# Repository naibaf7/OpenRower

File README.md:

# OpenRower

An open-source rowing monitor for any rowing machine. A sensor on the flywheel sends the timing of each
pulse to an Android app. The app works out pace, power, stroke rate and distance, draws a live force curve
and records your workouts.

## Features

- **Workout modes:** free rowing, set distance, set time, target pace, and custom interval workouts built
  from segments.
- **Live display:**
  - pace per 500 m (current and average), stroke rate, power in watts or calories;
  - time and distance, elapsed and remaining, and the projected finish;
  - heart rate.
- **Charts:** a force curve for every stroke, and a stroke-by-stroke bar chart of power with heart-rate zones.
- **Custom workouts:** a timeline editor with a target pace per segment, music per segment (matched to your
  stroke rate by BPM, from a folder or M3U playlist) and a spoken countdown.
- **Training history** with splits for every workout.
- **Heart rate** from BLE chest straps that use the standard Heart Rate service (developed with a Polar H7).
- **Physics:** the drag factor is measured on every stroke. Flywheel inertia and the distance factor are
  stored per machine profile. You can calibrate the distance factor against the machine's own monitor.
- **Built-in profiles** for the Concept2 Model C, D and E and the Infinity R70.
- **Test mode** with simulated data, so you can try the app without any hardware.

## Hardware

You need one of these to connect a rowing machine:

| | OpenRower sensor board | DIY Arduino build |
|---|---|---|
| Board | ESP32-C3 board in [`hardware/`](hardware/openrower_sensor_circuit.md) | Arduino Nano + BT05/HM-10 BLE module |
| Sensor | Plug the machine's sensor into its 2.5 mm jack: hall sensors at 3.3 V or 5 V, Concept2 Model C pickup coil, Concept2 Model D/E generator | Hall sensor on pin 2, magnets on the flywheel (3 magnets 120° apart) |
| Link to the phone | BLE, or USB-C via USB-OTG | BLE, or USB via USB-OTG |
| Firmware | [`OpenRowerESP32/`](OpenRowerESP32/README.md) | [`OpenRowerArduino/`](OpenRowerArduino/OpenRowerArduino.ino) |

The app chooses the sensor board's input mode from the machine profile, or detects what is plugged in.
The board is designed so that no mode choice can damage it, the phone or the rowing machine. The one
exception is giving 5 V to a hall sensor that is only rated for 3.3 V, so the app asks before it switches
to 5 V.

## Getting started

1. **Install the app.** It needs Android 12 or newer. A Google Play release, published by Smartapes, is
   in preparation. Until then, build it from source: connect your phone with USB debugging on, then run
   ```
   ./gradlew installDebug
   ```
   or open the project in Android Studio and press Run.
2. **Set up the hardware.**
   - Sensor board: order it as described in
     [`hardware/openrower_sensor_circuit.md`](hardware/openrower_sensor_circuit.md) §9. Then flash the
     firmware image from the [releases page](https://github.com/naibaf7/OpenRower/releases), or build it
     yourself ([`OpenRowerESP32/README.md`](OpenRowerESP32/README.md)).
   - Arduino: wire up the hall sensor and BT module as described at the top of the sketch, then upload it.
     The sketch sets the BT module to the right baud rate by itself.
3. **In the app:**
   1. In **Settings**, pick or create a machine profile.
   2. Choose the rowing device (Scan BLE) and, for the sensor board, the sensor input.
   3. Go back to **Workout Setup**, pick a mode and start rowing.

To try the app without hardware, turn on **Test Mode** on the Workout Setup screen.

## Status

- **App and Arduino build:** in use on an Infinity R70 fitted with a hall sensor.
- **Sensor board (rev 2) and ESP32 firmware:** designed, and the firmware compiles, but neither has been
  tested on real hardware yet. Start with the bring-up checklist in
  [`hardware/openrower_sensor_circuit.md`](hardware/openrower_sensor_circuit.md) §10.
- **Concept2 profiles:** the constants come from OpenRowingMonitor's rower profiles and have not been checked
  on a real machine yet.

## Repository layout

| Path | Contents |
|---|---|
| `app/` | Android app (Kotlin) |
| `OpenRowerESP32/` | Firmware for the sensor board and the serial/BLE protocol |
| `OpenRowerArduino/` | Firmware for the Arduino Nano + BT05 build |
| `hardware/` | Sensor board: KiCad schematic and routed board, schematic PDF, generator scripts, design notes. Production files (gerbers, BOM, CPL) are on the releases page. |

## Privacy

OpenRower has no internet access. Your workouts stay on your device. See [PRIVACY.md](PRIVACY.md).

## Contributing

Contributions are welcome. See [CONTRIBUTING.md](CONTRIBUTING.md). Maintainers release as described in
[RELEASING.md](RELEASING.md).

## License

- **Software** (the app, both firmwares, `hardware/tools/`): [MIT](LICENSE). Third-party licences: in the
  app under Settings → Open-Source Licenses, and for firmware images in
  [OpenRowerESP32/THIRD_PARTY_NOTICES.txt](OpenRowerESP32/THIRD_PARTY_NOTICES.txt).
- **Hardware** (the sensor board design in `hardware/`): [CERN-OHL-S v2](hardware/LICENSE). If you make
  boards for others, keep the source location visible; see [hardware/NOTICE](hardware/NOTICE).

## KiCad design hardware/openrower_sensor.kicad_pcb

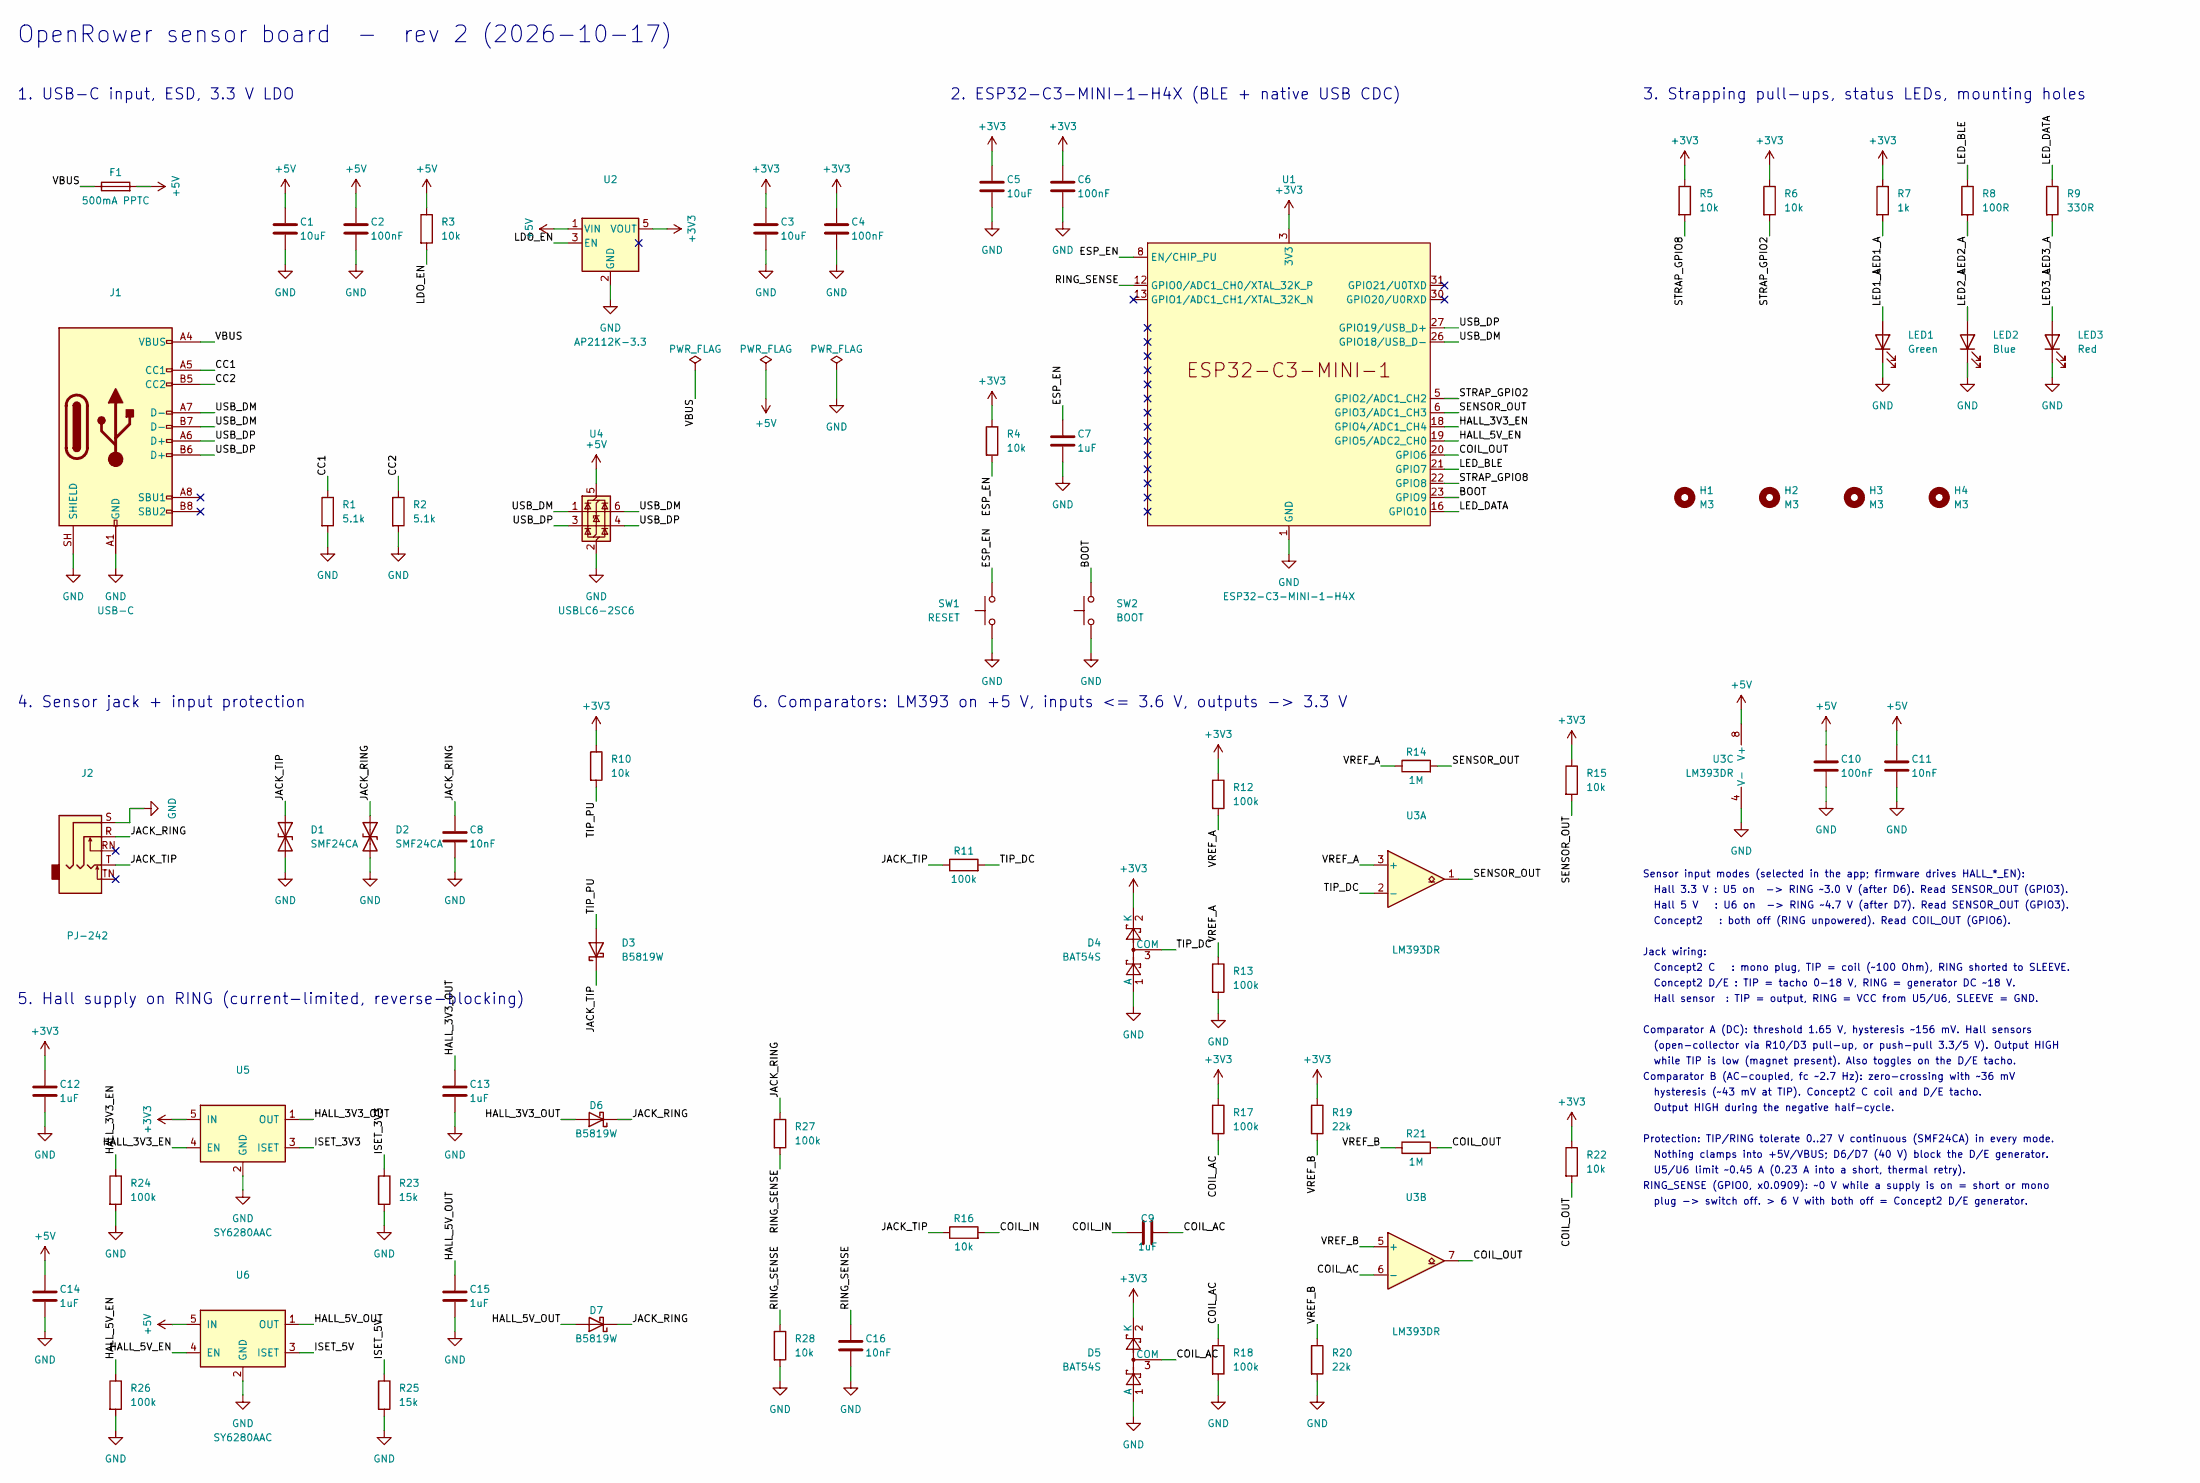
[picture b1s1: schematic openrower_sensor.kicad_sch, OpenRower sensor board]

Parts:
C1, C3, C5: 10uF; C_0603_1608Metric; MPN CL10A106KP8NNNC; LCSC C19702
C2, C4, C6, C10: 100nF; C_0402_1005Metric; MPN CL05B104KO5NNNC; LCSC C1525
C7, C12, C13, C14, C15: 1uF; C_0402_1005Metric; MPN CL05A105KA5NQNC; LCSC C52923
C8, C11, C16: 10nF; C_0402_1005Metric; MPN CL05B103KB5NNNC; LCSC C15195
C9: 1uF; C_0603_1608Metric; MPN CL10A105KB8NNNC; LCSC C15849
D1, D2: SMF24CA; D_SOD-123F; MPN SMF24CA; LCSC C123811
D3, D6, D7: B5819W; D_SOD-123; MPN B5819W SL; LCSC C8598
D4, D5: BAT54S; SOT-23; MPN BAT54S,215; LCSC C47546
F1: 500mA PPTC; Fuse_1206_3216Metric; MPN nSMD050-33V; LCSC C70077
H1, H2, H3, H4: M3; MountingHole_3.2mm_M3
J1: USB-C; USB_C_Receptacle_HRO_TYPE-C-31-M-12_Edge; MPN TYPE-C-31-M-12; LCSC C165948
J2: PJ-242; Jack_2.5mm_SHOUHAN_PJ-242; MPN PJ-242; LCSC C431536
LED1: Green; LED_0603_1608Metric; MPN XL-1608UGC-04; LCSC C965804
LED2: Blue; LED_0603_1608Metric; MPN XL-1608UBC-04; LCSC C965807
LED3: Red; LED_0603_1608Metric; MPN KT-0603R; LCSC C2286
R1, R2: 5.1k; R_0402_1005Metric; MPN 0402WGF5101TCE; LCSC C25905
R3, R4, R5, R6, R10, R15, R22, R28: 10k; R_0402_1005Metric; MPN 0402WGF1002TCE; LCSC C25744
R7: 1k; R_0402_1005Metric; MPN 0402WGF1001TCE; LCSC C11702
R8: 100R; R_0402_1005Metric; MPN 0402WGF1000TCE; LCSC C25076
R9: 330R; R_0402_1005Metric; MPN 0402WGF3300TCE; LCSC C25104
R11, R12, R13, R17, R18, R24, R26, R27: 100k; R_0402_1005Metric; MPN 0402WGF1003TCE; LCSC C25741
R14, R21: 1M; R_0402_1005Metric; MPN 0402WGF1004TCE; LCSC C26083
R16: 10k; R_0603_1608Metric; MPN 0603WAF1002T5E; LCSC C25804
R19, R20: 22k; R_0402_1005Metric; MPN 0402WGF2202TCE; LCSC C25768
R23, R25: 15k; R_0402_1005Metric; MPN 0402WGF1502TCE; LCSC C25756
SW1: RESET; SW_Push_1P1T_XKB_TS-1187A; MPN TS-1187A-B-A-B; LCSC C318884
SW2: BOOT; SW_Push_1P1T_XKB_TS-1187A; MPN TS-1187A-B-A-B; LCSC C318884
U1: ESP32-C3-MINI-1-H4X; ESP32-C3-MINI-1; MPN ESP32-C3-MINI-1-H4X; LCSC C41349510
U2: AP2112K-3.3; SOT-23-5; MPN AP2112K-3.3TRG1; LCSC C51118
U3: LM393DR; SOIC-8_3.9x4.9mm_P1.27mm; MPN LM393DR; LCSC C67470
U4: USBLC6-2SC6; SOT-23-6; MPN USBLC6-2SC6; LCSC C7519
U5, U6: SY6280AAC; SOT-23-5; MPN SY6280AAC; LCSC C55136

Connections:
+3V3: C3.1, C4.1, C5.1, C6.1, C12.1, D4.2 (K), D5.2 (K), R4.1, R5.1, R6.1, R7.1, R10.1, R12.1, R15.1, R17.1, R19.1, R22.1, U1.3 (3V3), U2.5 (VOUT), U5.5 (IN)
+5V: C1.1, C2.1, C10.1, C11.1, C14.1, F1.2, R3.1, U2.1 (VIN), U3.8 (V+), U4.5 (VBUS), U6.5 (IN)
/BOOT: SW2.2, U1.23 (GPIO9)
/CC1: J1.A5 (CC1), R1.1
/CC2: J1.B5 (CC2), R2.1
/COIL_AC: C9.2, D5.3 (COM), R17.2, R18.1, U3.6 (-)
/COIL_IN: C9.1, R16.2
/COIL_OUT: R21.2, R22.2, U1.20 (GPIO6), U3.7
/ESP_EN: C7.1, R4.2, SW1.2, U1.8 (EN/CHIP_PU)
/HALL_3V3_EN: R24.1, U1.18 (GPIO4/ADC1_CH4), U5.4 (EN)
/HALL_3V3_OUT: C13.1, D6.2 (A), U5.1 (OUT)
/HALL_5V_EN: R26.1, U1.19 (GPIO5/ADC2_CH0), U6.4 (EN)
/HALL_5V_OUT: C15.1, D7.2 (A), U6.1 (OUT)
/ISET_3V3: R23.1, U5.3 (ISET)
/ISET_5V: R25.1, U6.3 (ISET)
/JACK_RING: C8.1, D2.1 (A1), D6.1 (K), D7.1 (K), J2.R, R27.1
/JACK_TIP: D1.1 (A1), D3.1 (K), J2.T, R11.1, R16.1
/LDO_EN: R3.2, U2.3 (EN)
/LED1_A: LED1.2 (A), R7.2
/LED2_A: LED2.2 (A), R8.2
/LED3_A: LED3.2 (A), R9.2
/LED_BLE: R8.1, U1.21 (GPIO7)
/LED_DATA: R9.1, U1.16 (GPIO10)
/RING_SENSE: C16.1, R27.2, R28.1, U1.12 (GPIO0/ADC1_CH0/XTAL_32K_P)
/SENSOR_OUT: R14.2, R15.2, U1.6 (GPIO3/ADC1_CH3), U3.1
/STRAP_GPIO2: R6.2, U1.5 (GPIO2/ADC1_CH2)
/STRAP_GPIO8: R5.2, U1.22 (GPIO8)
/TIP_DC: D4.3 (COM), R11.2, U3.2 (-)
/TIP_PU: D3.2 (A), R10.2
/USB_DM: J1.A7 (D-), J1.B7 (D-), U1.26 (GPIO18/USB_D-), U4.1 (I/O1), U4.6 (I/O1)
/USB_DP: J1.A6 (D+), J1.B6 (D+), U1.27 (GPIO19/USB_D+), U4.3 (I/O2), U4.4 (I/O2)
/VBUS: F1.1, J1.A4 (VBUS), J1.A9 (VBUS), J1.B4 (VBUS), J1.B9 (VBUS)
/VREF_A: R12.2, R13.1, R14.1, U3.3 (+)
/VREF_B: R19.2, R20.1, R21.1, U3.5 (+)
GND: C1.2, C2.2, C3.2, C4.2, C5.2, C6.2, C7.2, C8.2, C10.2, C11.2, C12.2, C13.2, C14.2, C15.2, C16.2, D1.2 (A2), D2.2 (A2), D4.1 (A), D5.1 (A), J1.A1 (GND), J1.A12 (GND), J1.B1 (GND), J1.B12 (GND), J1.SH (SHIELD), J2.S, LED1.1 (K), LED2.1 (K), LED3.1 (K), R1.2, R2.2, R13.2, R18.2, R20.2, R23.2, R24.2, R25.2, R26.2, R28.2, SW1.1, SW2.1, U1.1 (GND), U1.2 (GND), U1.11 (GND), U1.14 (GND), U1.36 (GND), U1.37 (GND), U1.38 (GND), U1.39 (GND), U1.40 (GND), U1.41 (GND), U1.42 (GND), U1.43 (GND), U1.44 (GND), U1.45 (GND), U1.46 (GND), U1.47 (GND), U1.48 (GND), U1.49 (GND), U1.50 (GND), U1.51 (GND), U1.52 (GND), U1.53 (GND), U2.2 (GND), U3.4 (V-), U4.2 (GND), U5.2 (GND), U6.2 (GND)

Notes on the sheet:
OpenRower sensor board - rev 2 (2026-10-17)
1. USB-C input, ESD, 3.3 V LDO
2. ESP32-C3-MINI-1-H4X (BLE + native USB CDC)
3. Strapping pull-ups, status LEDs, mounting holes
4. Sensor jack + input protection
5. Hall supply on RING (current-limited, reverse-blocking)
6. Comparators: LM393 on +5 V, inputs <= 3.6 V, outputs -> 3.3 V
Sensor input modes (selected in the app; firmware drives HALL_*_EN):
Hall 3.3 V : U5 on -> RING ~3.0 V (after D6). Read SENSOR_OUT (GPIO3).
Hall 5 V : U6 on -> RING ~4.7 V (after D7). Read SENSOR_OUT (GPIO3).
Concept2 : both off (RING unpowered). Read COIL_OUT (GPIO6).
Jack wiring:
Concept2 C : mono plug, TIP = coil (~100 Ohm), RING shorted to SLEEVE.
Concept2 D/E : TIP = tacho 0-18 V, RING = generator DC ~18 V.
Hall sensor : TIP = output, RING = VCC from U5/U6, SLEEVE = GND.
Comparator A (DC): threshold 1.65 V, hysteresis ~156 mV. Hall sensors
(open-collector via R10/D3 pull-up, or push-pull 3.3/5 V). Output HIGH
while TIP is low (magnet present). Also toggles on the D/E tacho.
Comparator B (AC-coupled, fc ~2.7 Hz): zero-crossing with ~36 mV
hysteresis (~43 mV at TIP). Concept2 C coil and D/E tacho.
Output HIGH during the negative half-cycle.
Protection: TIP/RING tolerate 0..27 V continuous (SMF24CA) in every mode.
Nothing clamps into +5V/VBUS; D6/D7 (40 V) block the D/E generator.
U5/U6 limit ~0.45 A (0.23 A into a short, thermal retry).
RING_SENSE (GPIO0, x0.0909): ~0 V while a supply is on = short or mono
plug -> switch off. > 6 V with both off = Concept2 D/E generator.

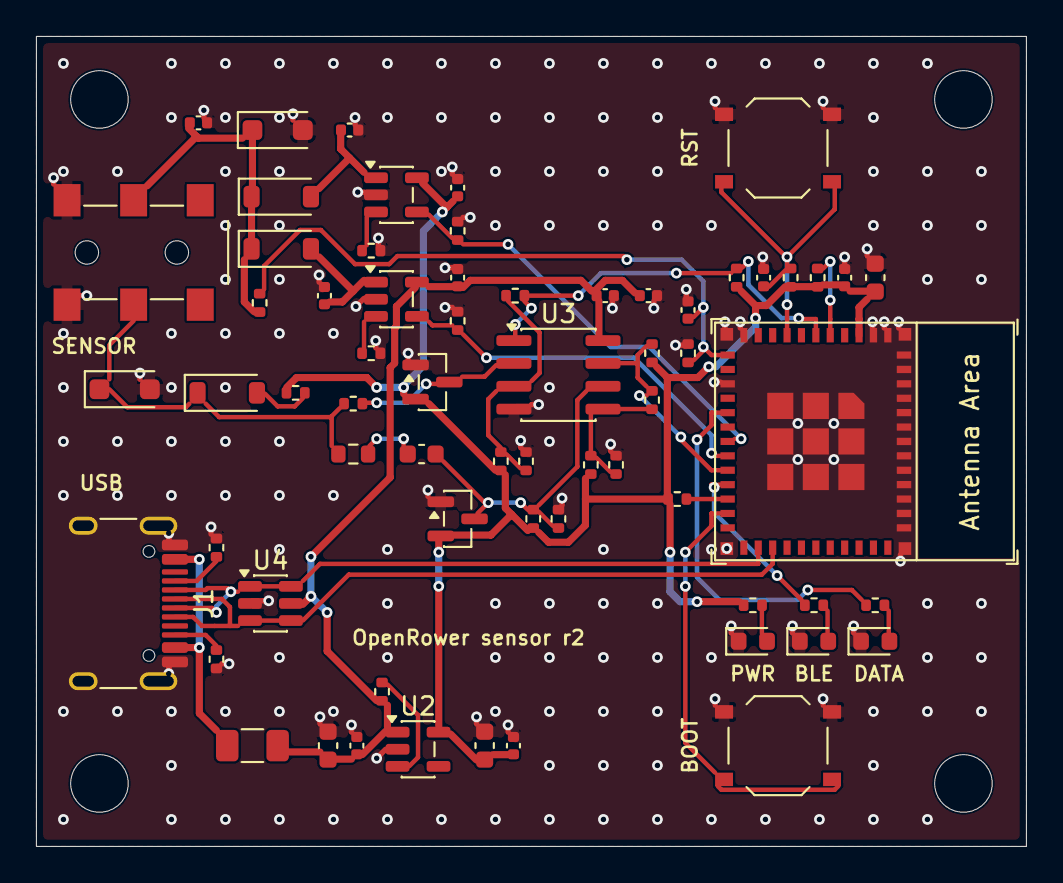
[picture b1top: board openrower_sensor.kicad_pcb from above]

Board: 2 copper layers, 55.0 x 45.0 mm, 69 parts (0 on the bottom side), 35 nets.

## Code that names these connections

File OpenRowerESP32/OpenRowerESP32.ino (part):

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 * native USB (CDC serial, e.g. a phone on USB-OTG).  Both outputs carry the same text protocol.
 *
 * ── Board pins (hardware/openrower_sensor_circuit.md) ───────────────────────────────────────
 *   GPIO3  SENSOR_OUT   comparator A (DC, 1.65 V threshold): hall sensors. HIGH while the hall
 *                       output is low, so a RISING edge = magnet arrives.
 *   GPIO6  COIL_OUT     comparator B (AC-coupled zero crossing): Concept2 coil / tacho.
 *   GPIO4  HALL_3V3_EN  SY6280 load switch: 3.3 V onto the jack RING (active high, pulled down)
 *   GPIO5  HALL_5V_EN   SY6280 load switch: 5 V onto the jack RING (active high, pulled down)
 *   GPIO0  RING_SENSE   ADC, RING voltage x 10/110
 *   GPIO7  LED_BLE      blue, GPIO10 LED_DATA red
 *
 * ── Protocol (one line each, '\n' terminated) ───────────────────────────────────────────────
 *   board -> app
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#define TEST_MODE   0         // 1 = synthetic pulses (no sensor needed), like OpenRowerArduino

// ── Pins ─────────────────────────────────────────────────────────────────────────────────
static const int PIN_SENSOR_OUT  = 3;
static const int PIN_COIL_OUT    = 6;
static const int PIN_HALL3V3_EN  = 4;
static const int PIN_HALL5V_EN   = 5;
static const int PIN_RING_SENSE  = 0;
static const int PIN_LED_BLE     = 7;
static const int PIN_LED_DATA    = 10;

// ── Tuning ───────────────────────────────────────────────────────────────────────────────
static const float    RING_DIVIDER      = 11.0f;     // (100k + 10k) / 10k
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// ── RING measurement and supplies ────────────────────────────────────────────────────────
static int readRingMv() {
  uint32_t sum = 0;
  for (int i = 0; i < 8; i++) sum += analogReadMilliVolts(PIN_RING_SENSE);
  return (int)(sum / 8 * RING_DIVIDER);
}

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        g_state = ST_OK;
      }
    }
    attachSensor(PIN_SENSOR_OUT);
  } else {
    suppliesOff();
    g_ringMv = readRingMv();
    g_state = (g_mode == MODE_C2 && g_ringMv > RING_GEN_OFF_MV) ? ST_GENERATOR : ST_OK;
    attachSensor(g_mode == MODE_C2 ? PIN_COIL_OUT : -1);
  }
  return g_state != before || g_supplyOn != wasOn;
}
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static void updateLeds() {
  uint32_t now = millis();
  // BLE: solid while connected, short blink every 2 s while advertising
  digitalWrite(PIN_LED_BLE, g_bleConnected || (now % 2000) < 60 ? HIGH : LOW);
  // DATA: flash per pulse; 4 Hz blink while a hall supply is held off by a fault
  bool fault = (g_mode == MODE_HALL3V3 || g_mode == MODE_HALL5V) && g_state != ST_OK;
  if (fault) digitalWrite(PIN_LED_DATA, (now % 250) < 125 ? HIGH : LOW);
  else       digitalWrite(PIN_LED_DATA, now < g_dataLedOffMs ? HIGH : LOW);
}

// ── Pulses ───────────────────────────────────────────────────────────────────────────────
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  pinMode(PIN_HALL3V3_EN, OUTPUT);
  pinMode(PIN_HALL5V_EN, OUTPUT);
  suppliesOff();                                   // also held low by 100k pull-downs at reset
  pinMode(PIN_LED_BLE, OUTPUT);
  pinMode(PIN_LED_DATA, OUTPUT);
  pinMode(PIN_SENSOR_OUT, INPUT);                  // open-collector outputs, 10k pull-ups on board
  pinMode(PIN_COIL_OUT, INPUT);
  analogReadResolution(12);
  analogSetPinAttenuation(PIN_RING_SENSE, ADC_11db);   // 0..~2.5 V at the pin = RING 0..27 V

  setCpuFrequencyMhz(80);                          // lowest clock BLE and USB run at
  Serial.setTxTimeoutMs(0);                        // never block when no USB host listens
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
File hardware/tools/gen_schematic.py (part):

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# ── 2. ESP32-C3 module ─────────────────────────────────────────────────────────
esp = {str(n): 'GND' for n in [1, 2, 11, 14] + list(range(36, 54))}
esp.update({str(n): None for n in [4, 7, 9, 10, 15, 17, 24, 25, 28, 29, 32, 33, 34, 35, 13, 30, 31]})
esp.update({'3': '+3V3', '8': 'ESP_EN', '5': 'STRAP_GPIO2', '6': 'SENSOR_OUT', '12': 'RING_SENSE',
            '16': 'LED_DATA', '18': 'HALL_3V3_EN', '19': 'HALL_5V_EN', '20': 'COIL_OUT',
            '21': 'LED_BLE', '22': 'STRAP_GPIO8', '23': 'BOOT', '26': 'USB_DM', '27': 'USB_DP'})
part('U1', 'OpenRower:ESP32-C3-MINI-1', 'ESP32-C3-MINI-1-H4X', 'CustomFootprints:ESP32-C3-MINI-1',
     (248.92, 88.9), esp, lcsc='C41349510', mpn='ESP32-C3-MINI-1-H4X')
C('C5', '10uF', '+3V3', 'GND', (195.58, 53.34))
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     {'1': 'GND', '2': 'BOOT'}, rot=90, lcsc='C318884', mpn='TS-1187A-B-A-B')

# ── 3. strapping, LEDs, mounting holes ─────────────────────────────────────────
R('R5', '10k', '+3V3', 'STRAP_GPIO8', (320.04, 55.88))
R('R6', '10k', '+3V3', 'STRAP_GPIO2', (335.28, 55.88))
R('R7', '1k', '+3V3', 'LED1_A', (355.6, 55.88))
LED('LED1', 'Green', 'LED1_A', (355.6, 81.28), 'C965804', 'XL-1608UGC-04')
R('R8', '100R', 'LED_BLE', 'LED2_A', (370.84, 55.88))
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
NOTES = [
    'Sensor input modes (selected in the app; firmware drives HALL_*_EN):',
    '  Hall 3.3 V : U5 on  -> RING ~3.0 V (after D6). Read SENSOR_OUT (GPIO3).',
    '  Hall 5 V   : U6 on  -> RING ~4.7 V (after D7). Read SENSOR_OUT (GPIO3).',
    '  Concept2   : both off (RING unpowered). Read COIL_OUT (GPIO6).',
    '',
    'Jack wiring:',
    '  Concept2 C   : mono plug, TIP = coil (~100 Ohm), RING shorted to SLEEVE.',
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    'Protection: TIP/RING tolerate 0..27 V continuous (SMF24CA) in every mode.',
    '  Nothing clamps into +5V/VBUS; D6/D7 (40 V) block the D/E generator.',
    '  U5/U6 limit ~0.45 A (0.23 A into a short, thermal retry).',
    'RING_SENSE (GPIO0, x0.0909): ~0 V while a supply is on = short or mono',
    '  plug -> switch off. > 6 V with both off = Concept2 D/E generator.',
]

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
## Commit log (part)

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2026-04-20 Initial commit.
2026-04-21 Add icon.

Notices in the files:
hardware/openrower_sensor.kicad_pcb:
CERN-OHL-S-2.0
(c) 2026 Fabian Tschopp
